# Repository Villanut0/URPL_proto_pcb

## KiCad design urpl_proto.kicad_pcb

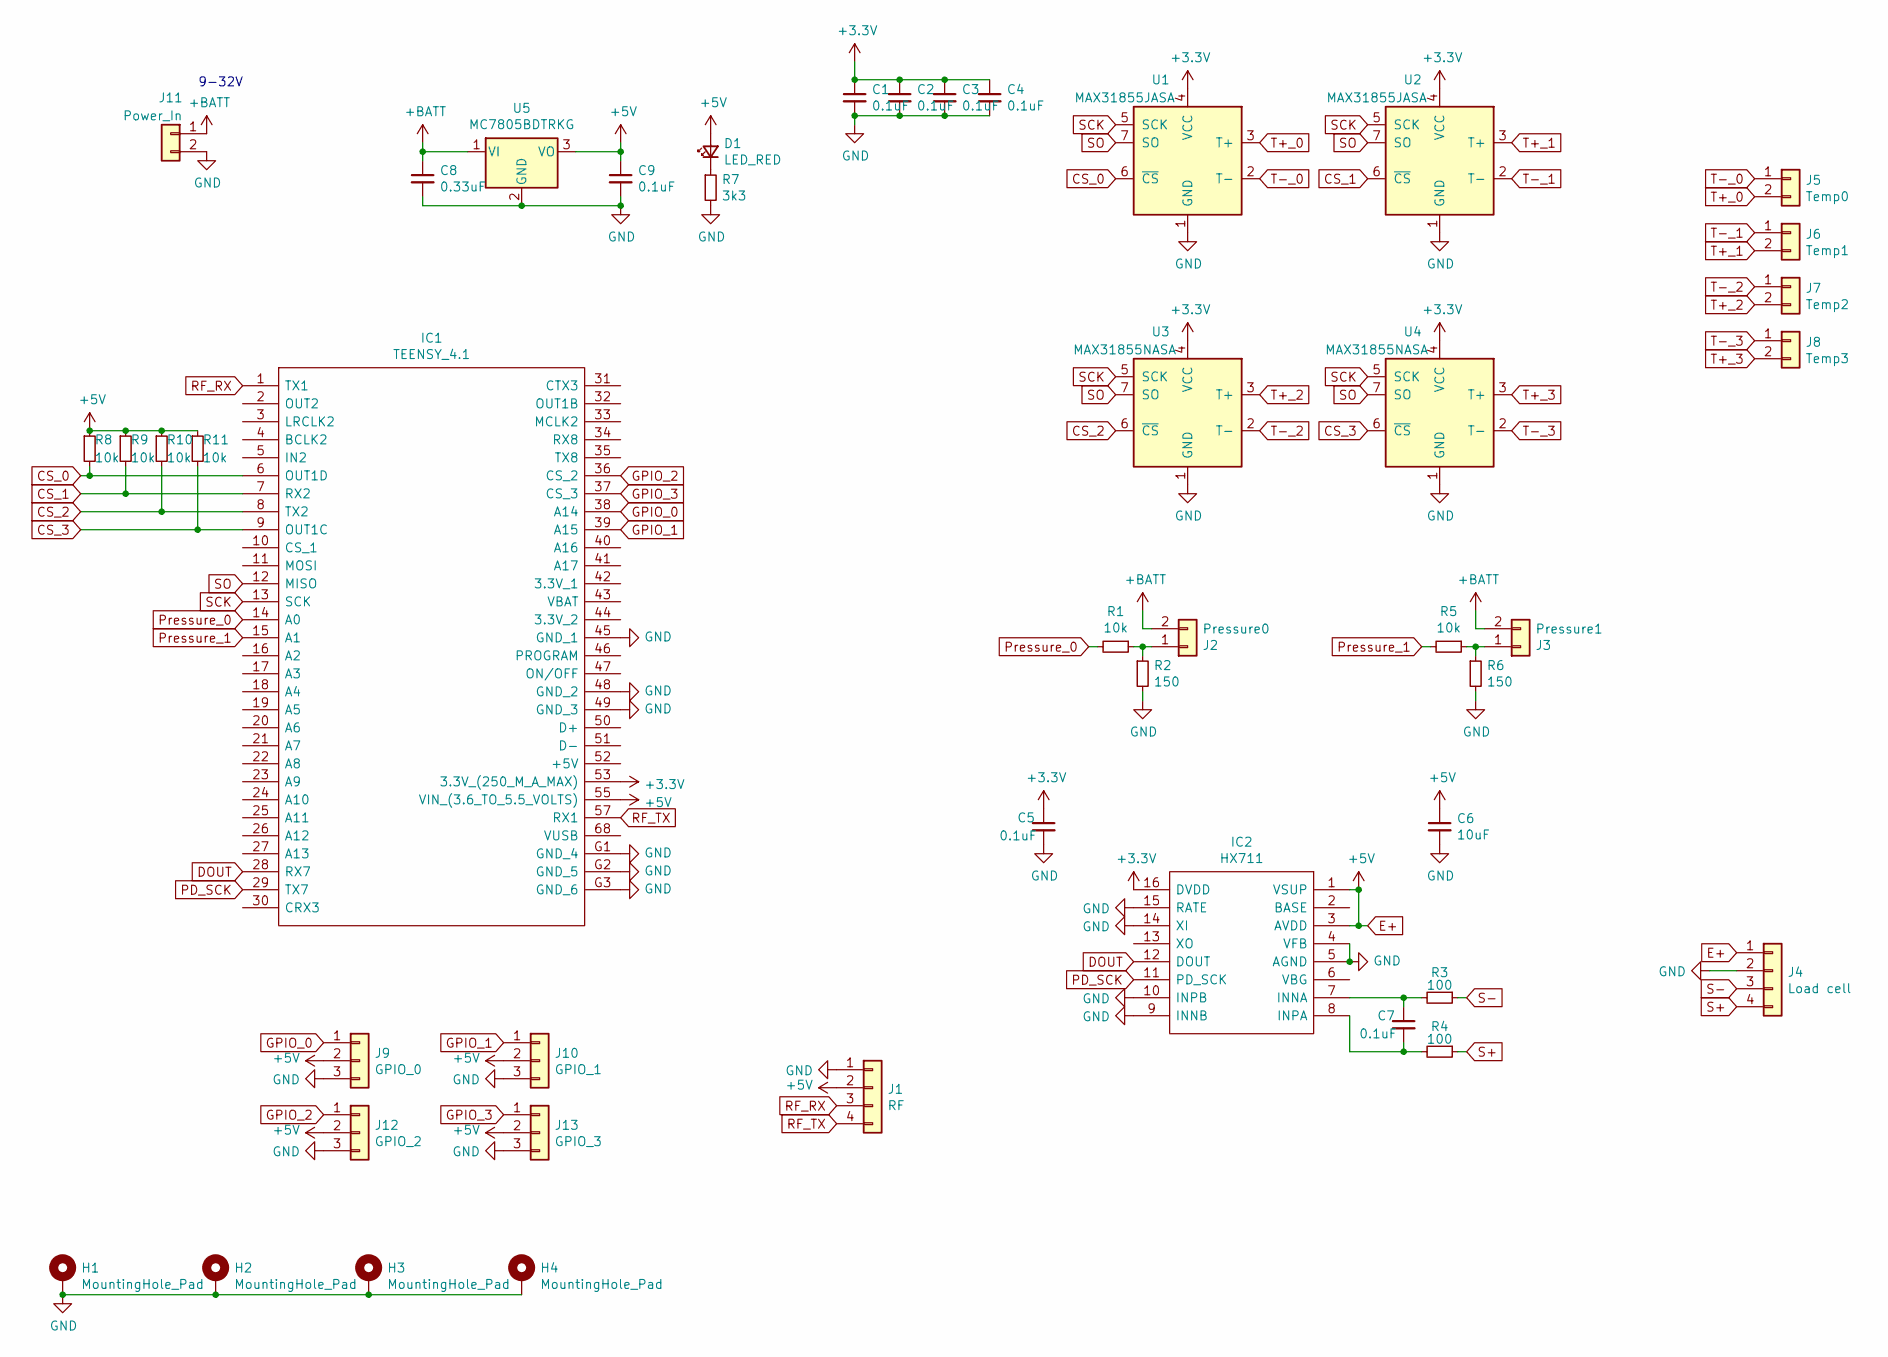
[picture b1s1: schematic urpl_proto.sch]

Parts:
C1, C2, C3, C4, C5, C7: 0.1uF; C_0805_2012Metric; LCSC C49678
C6: 10uF; C_0805_2012Metric; LCSC C15850
C8: 0.33uF; C_1206_3216Metric; LCSC C1740
C9: 0.1uF; C_0805_2012Metric; LCSC C24497
D1: LED_RED; LED_0805_2012Metric; LCSC C84256
H1, H2, H3, H4: MountingHole_Pad; MountingHole_2.2mm_M2_Pad_Via
IC1: TEENSY_4.1; TEENSY41; Manufacturer_Part_Number TEENSY 4.1
IC2: HX711; SOP-16_3.9x9.9mm_P1.27mm; Manufacturer_Part_Number HX711
J1: RF; PinHeader_1x04_P2.54mm_Vertical
J2: Pressure0; PhoenixContact_MC_1,5_2-G-3.5_1x02_P3.50mm_Horizontal
J3: Pressure1; PhoenixContact_MC_1,5_2-G-3.5_1x02_P3.50mm_Horizontal
J4: Load cell; PhoenixContact_MC_1,5_4-G-3.5_1x04_P3.50mm_Horizontal
J5: Temp0; PhoenixContact_MC_1,5_2-G-3.5_1x02_P3.50mm_Horizontal
J6: Temp1; PhoenixContact_MC_1,5_2-G-3.5_1x02_P3.50mm_Horizontal
J7: Temp2; PhoenixContact_MC_1,5_2-G-3.5_1x02_P3.50mm_Horizontal
J8: Temp3; PhoenixContact_MC_1,5_2-G-3.5_1x02_P3.50mm_Horizontal
J9: GPIO_0; PinHeader_1x03_P2.54mm_Vertical
J10: GPIO_1; PinHeader_1x03_P2.54mm_Vertical
J11: Power_In; PhoenixContact_MSTBA_2,5_2-G_1x02_P5.00mm_Horizontal
J12: GPIO_2; PinHeader_1x03_P2.54mm_Vertical
J13: GPIO_3; PinHeader_1x03_P2.54mm_Vertical
R1, R5, R8, R9, R10, R11: 10k; R_0805_2012Metric; LCSC C17414
R2, R6: 150; R_0805_2012Metric; LCSC C17471
R3, R4: 100; R_0805_2012Metric; LCSC C17408
R7: 3k3; R_0805_2012Metric; LCSC C26010
U1, U2: MAX31855JASA; SOIC-8_3.9x4.9mm_P1.27mm
U3, U4: MAX31855NASA; SOIC-8_3.9x4.9mm_P1.27mm
U5: MC7805BDTRKG; TO-252-2; LCSC C110908

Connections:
+3V3: C1.1, C2.1, C3.1, C4.1, C5.1, IC1.53 (3.3V_(250_M_A_MAX)), IC2.16 (DVDD), U1.4 (VCC), U2.4 (VCC), U3.4 (VCC), U4.4 (VCC)
+BATT: C8.1, J2.2, J3.2, J11.1, U5.1 (VI)
CS_0: IC1.6 (OUT1D), R8.2, U1.6 (~CS~)
CS_1: IC1.7 (RX2), R9.2, U2.6 (~CS~)
CS_2: IC1.8 (TX2), R10.2, U3.6 (~CS~)
CS_3: IC1.9 (OUT1C), R11.2, U4.6 (~CS~)
DOUT: IC1.28 (RX7), IC2.12 (DOUT)
E+: C6.1, C9.1, D1.2 (A), IC1.55 (VIN_(3.6_TO_5.5_VOLTS)), IC2.1 (VSUP), IC2.3 (AVDD), J1.2, J4.1, J9.2, J10.2, J12.2, J13.2, R8.1, R9.1, R10.1, R11.1, U5.3 (VO)
GND: C1.2, C2.2, C3.2, C4.2, C5.2, C6.2, C8.2, C9.2, H1.1, H2.1, H3.1, H4.1, IC1.45 (GND_1), IC1.48 (GND_2), IC1.49 (GND_3), IC1.G1 (GND_4), IC1.G2 (GND_5), IC1.G3 (GND_6), IC2.4 (VFB), IC2.5 (AGND), IC2.9 (INNB), IC2.10 (INPB), IC2.14 (XI), IC2.15 (RATE), J1.1, J4.2, J9.3, J10.3, J11.2, J12.3, J13.3, R2.2, R6.2, R7.2, U1.1 (GND), U2.1 (GND), U3.1 (GND), U4.1 (GND), U5.2 (GND)
GPIO_0: IC1.38 (A14), J9.1
GPIO_1: IC1.39 (A15), J10.1
GPIO_2: IC1.36 (CS_2), J12.1
GPIO_3: IC1.37 (CS_3), J13.1
unnamed: C7.1, IC2.7 (INNA), R3.2
unnamed: C7.2, IC2.8 (INPA), R4.2
unnamed: D1.1 (K), R7.1
unnamed: J2.1, R1.1, R2.1
unnamed: J3.1, R5.1, R6.1
PD_SCK: IC1.29 (TX7), IC2.11 (PD_SCK)
Pressure_0: IC1.14 (A0), R1.2
Pressure_1: IC1.15 (A1), R5.2
RF_RX: IC1.1 (TX1), J1.3
RF_TX: IC1.57 (RX1), J1.4
S+: J4.4, R4.1
S-: J4.3, R3.1
SCK: IC1.13 (SCK), U1.5 (SCK), U2.5 (SCK), U3.5 (SCK), U4.5 (SCK)
SO: IC1.12 (MISO), U1.7 (SO), U2.7 (SO), U3.7 (SO), U4.7 (SO)
T+_0: J5.2, U1.3 (T+)
T+_1: J6.2, U2.3 (T+)
T+_2: J7.2, U3.3 (T+)
T+_3: J8.2, U4.3 (T+)
T-_0: J5.1, U1.2 (T-)
T-_1: J6.1, U2.2 (T-)
T-_2: J7.1, U3.2 (T-)
T-_3: J8.1, U4.2 (T-)

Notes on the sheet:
9-32V

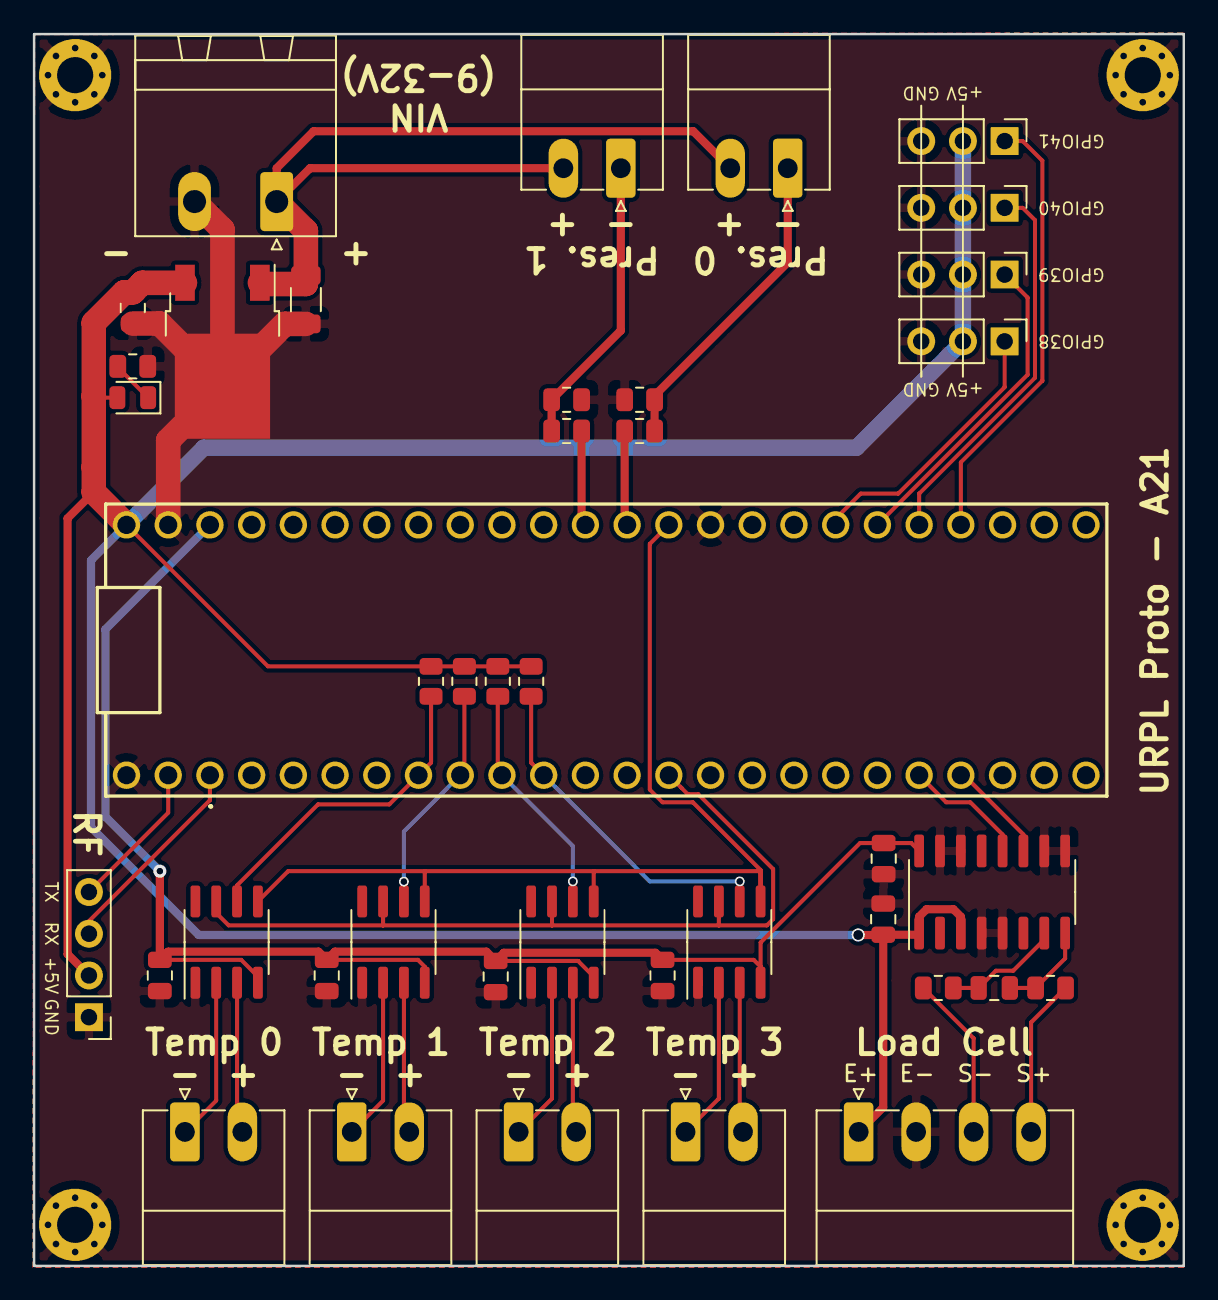
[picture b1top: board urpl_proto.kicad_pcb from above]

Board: 2 copper layers, 70.0 x 75.0 mm, 45 parts (0 on the bottom side), 35 nets.

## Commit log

2022-01-10 Add schematic pdf
